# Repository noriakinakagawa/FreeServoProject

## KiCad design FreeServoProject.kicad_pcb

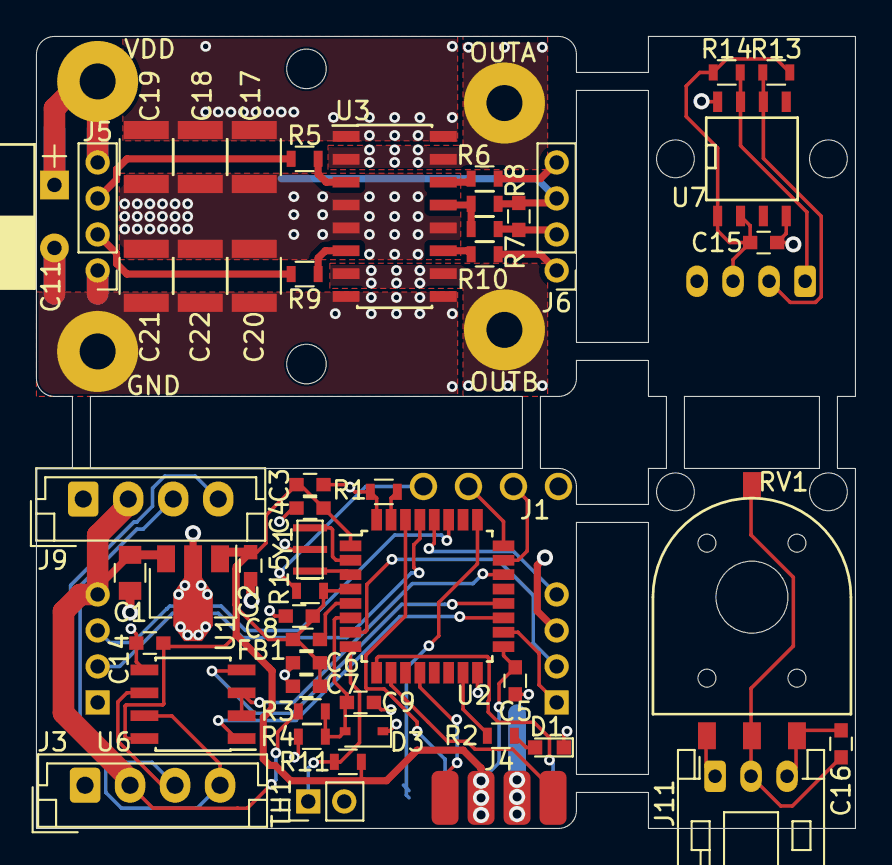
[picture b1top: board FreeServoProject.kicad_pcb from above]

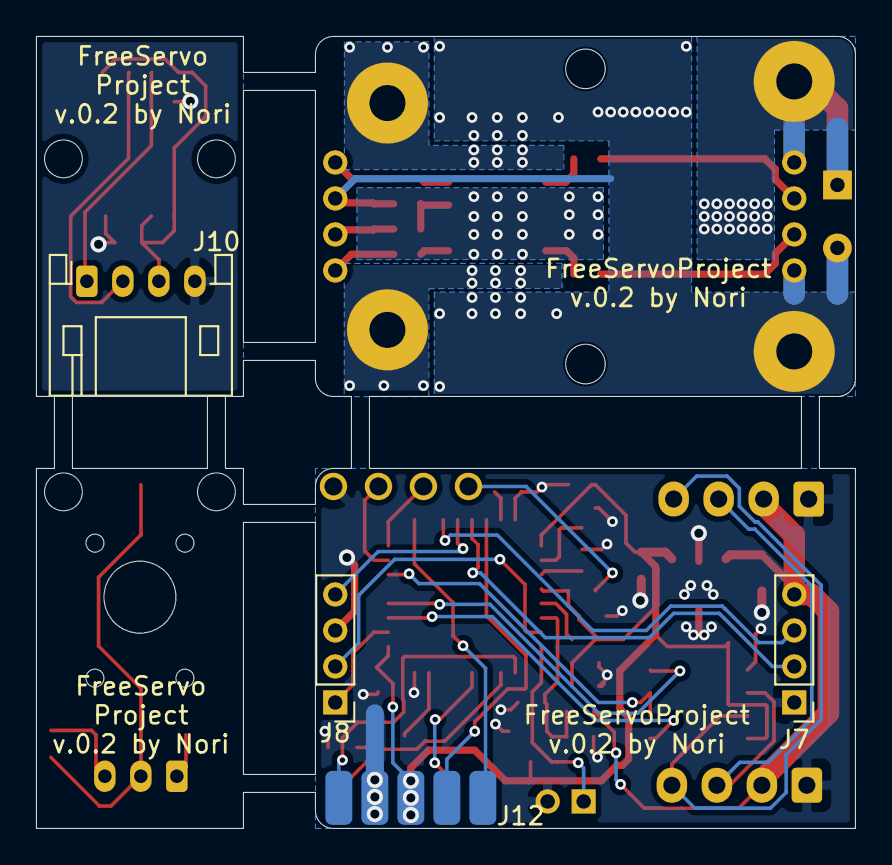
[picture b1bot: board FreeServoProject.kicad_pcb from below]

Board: 2 copper layers, 45.5 x 44.0 mm, 60 parts (4 on the bottom side), 36 nets.

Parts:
C1: 1u35V; C_0805
C2: 2.2u; C_0603
C3: 1u; C_0603
C4, C5, C7, C8, C9, C14, C15, C16: 0.1u; C_0603
C6: 0.01u; C_0603
C10: 33n; C_0603
C11: 220u35V; CP_Radial_D8.0mm_P3.50mm
C17, C18, C19, C20, C21, C22: 10u35V; C_1210
D1: LED; LED_0603
D3: D_TVS; D_SOD-323
FB1: Ferrite_Bead; C_0603
H1, H2, H3, H4: MountingHole_Pad; SolderWirePad_single_2mmDrill
J1: 4P-SBN
J3, J9: Conn_01x04; JST_EH_B4B-EH-A_1x04_P2.50mm_Vertical
J4: 4_SMD_Pad
J5, J6: Pin_Header_Straight_1x04_Pitch2.00mm
J7, J8: Socket_Strip_Straight_1x04_Pitch2.00mm
J10: S4B-PH-K; JST_PH_S4B-PH-K_1x04_P2.00mm_Horizontal
J11: S3B-PH-K; JST_PH_S3B-PH-K_1x03_P2.00mm_Horizontal
J12: 5_SMD_Pad
R1, R2, R7, R13, R14, R15: 10k; R_0603
R3, R11: 6.8k 1%; R_0603
R4: 910 1%; R_0603
R5, R6, R9, R10: 1k; R_0603
R8: 1.5k 1%; R_0603
RV1: RDC503052A
TH1: RTH103AT; Pin_Header_Straight_1x02_Pitch2.00mm
U1: AP7381-33Y-13; SOT-89-3
U2: STM32F303K8Tx; LQFP-32_7x7mm_Pitch0.8mm
U3: VNH7070BASTR; SOIC-16_3.9x9.9mm_Pitch1.27mm
U6: ST1480ACDR; SOIC-8_3.9x4.9mm_Pitch1.27mm
U7: AS5600-ASOM; SOIC-8-N
Y1: Resonator; CSTNE8M00G55Z000R0

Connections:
+3V3: C2.1, C3.1, C4.1, C5.1, C6.1, C7.1, C8.1, C14.1, C15.1, FB1.1, J4.2, J10.3, J11.1, J12.3, R11.1, R13.1, R14.1, R15.2, RV1.1, U1.1, U2.1, U2.4, U2.17, U6.8, U7.1, U7.2
+BATT: C1.1, C11.1, C17.1, C18.1, C19.1, C20.1, C21.1, C22.1, H3.1, J3.2, J5.4, J7.4, J9.2, R3.1, U1.3, U3.4, U3.5, U3.12
CS: C10.1, J6.2, J8.2, R7.2, U2.7
DE: U2.22, U6.2, U6.3
ENC_A: J4.1, U2.12
ENC_B: J4.4, U2.10
GND: C1.2, C2.2, C3.2, C4.2, C5.2, C6.2, C7.2, C8.2, C9.2, C10.2, C11.2, C14.2, C15.2, C16.2, C17.2, C18.2, C19.2, C20.2, C21.2, C22.2, D1.1, D3.1, H4.1, J1.1, J3.1, J4.3, J5.1, J6.3, J7.1, J8.3, J9.1, J10.4, J11.3, J12.4, R1.2, R4.2, R8.1, RV1.3, TH1.2, U1.2, U2.16, U2.32, U3.1, U3.8, U3.9, U3.16, U6.5, U7.4, U7.8, Y1.2
INA: J5.3, J7.3, R5.1, U2.27
INB: J5.2, J7.2, R9.1, U2.29
LED: R2.1, U2.15
unnamed: D1.2, R2.2
unnamed: FB1.2, U2.5
unnamed: R1.1, U2.31
unnamed: R5.2, U3.3
unnamed: R6.1, U3.14
unnamed: R7.1, R8.2, U3.13
unnamed: R9.2, U3.6
unnamed: R10.1, U3.11
unnamed: U2.2, Y1.1
unnamed: U2.3, Y1.3
OUTA: H1.1, U3.2, U3.15
OUTB: H2.1, U3.7, U3.10
PWM: J6.1, J8.1, R10.2, U2.18
Potentiometer: C16.1, J11.2, J12.5, RV1.2, U2.9
RS485_D+: J3.3, J9.3, U6.6
RS485_D-: J3.4, J9.4, U6.7
RST: J1.4, R15.1
RX: U2.19, U6.1
SCL: J10.1, J12.1, R14.2, U2.25, U7.7
SDA: J10.2, J12.2, R13.2, U2.30, U7.6
SEL0: J6.4, J8.4, R6.2, U2.28
SWCLK: J1.3, U2.24
SWDIO: J1.2, U2.23
TEMP: R11.2, TH1.1, U2.8
TX: U2.20, U6.4
Volt: C9.1, D3.2, R3.2, R4.1, U2.6

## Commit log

2021-04-11 Add files
2021-04-18 Add files via upload
    フットプリント追加と基板設計前。
2021-07-11 fix ver.0.2
